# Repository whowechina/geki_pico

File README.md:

# Geki Pico - ONGEKI Style Mini Controller
[点这里可以切换到中文版](README_CN.md)

Features:
* It's small but closely replicates the feel of the arcade controller.
* Smooth lever action with adjustable resistance.
* Air WAD with sound feedback.
* IO4 emulation.
* Built-in AIME card reader.
* Command line for configurations.
* All source files open.

Thanks to many respectful guys/companies who made their tools or materials free or open source (KiCad, OnShape, InkScape, Raspberry things).

Special thanks to community projects and developers.

* Robin Grosset (https://github.com/rgrosset/pico-pwm-audio)
* GEEKiDoS (https://github.com/GEEKiDoS/ongeeki-firmware)
* Pololu (https://github.com/pololu/vl53l0x-arduino, https://github.com/pololu/vl53l1x-arduino)
* RP_Silicon_KiCad: https://github.com/HeadBoffin/RP_Silicon_KiCad
* Type-C: https://github.com/ai03-2725/Type-C.pretty
* Chris Veigl (https://github.com/ChrisVeigl/ESP32Sound)

## My Other Projects
You can check out my other cool projects.

* Popn Pico: https://github.com/whowechina/popn_pico
* IIDX Pico: https://github.com/whowechina/iidx_pico
* IIDX Teeny: https://github.com/whowechina/iidx_teeny
* Chu Pico: https://github.com/whowechina/chu_pico
* Mai Pico: https://github.com/whowechina/mai_pico
* Diva Pico: https://github.com/whowechina/diva_pico
* AIC Pico: https://github.com/whowechina/aic_pico
* Groove Pico: https://github.com/whowechina/groove_pico
* Geki Pico: https://github.com/whowechina/geki_pico
* Musec Pico: https://github.com/whowechina/musec_pico
* Ju Pico: https://github.com/whowechina/ju_pico
* Bishi Pico: https://github.com/whowechina/bishi_pico
* Bishi Pico: https://github.com/whowechina/nos_pico

## **Disclaimer** ##
I made this project in my personal time with no financial benefit or sponsorship. I will continue to improve the project. I have done my best to ensure that everything is accurate and functional, there's always a chance that mistakes may occur. I cannot be held responsible for any loss of your time or money that may result from using this open source project. Thank you for your understanding.

## About the License
It's CC-NC. So DIY for yourself and for your friend, don't make money from it. And plagiarism that doesn’t even dare to mention the original author is not acceptable. Plase note that pooling orders and group buying for raw materials is acceptable. Selling off any leftover components without profit is also acceptable.

If you're interested in buying from me or some kind of commercial use, please contact me (Discord, QQ group, Wechat group or leave your contact in issue section).

## My Discord Invitation
https://discord.gg/M8f2PPQFEA

## HOW TO BUILD
### PCB and Components
* Go JLCPCB and make order with the gerber zip file (latest `Production\PCB\geki_main_xxx.zip`), regular FR-4 board, black or white color, **1.6mm** thickness.  
  
* 1x Rasberry Pico Pi Pico or pin-to-pin compatible clones (U1).  
  https://www.raspberrypi.com/products/raspberry-pi-pico
* 1x USB Type-C socket (918-418K2023S40001 or KH-TYPE-C-16P)
* 35x WS2812B-4020 side-facing RGB LEDs (D2-D36). Be careful with the orientation when soldering: D2 to D4 and D34 to D36 should be facing sideways, while the others should be facing up.  
  https://www.lcsc.com/product-detail/Light-Emitting-Diodes-LED_Worldsemi-WS2812B-4020_C965557.html
* 2x WS2812B-3528 RGB LEDs (D1, D37).
* 2x 8002A audio mini amplifier board (AMP1, AMP2), or you can use discrete components following the schematics (R4, R5, R8, R9, C9 ~ 12).  
    
  https://www.nz-electronics.co.nz/products/4pcs-one-sell-3v-5v-supply-voltage-3w-8002-audio-player-power-amplifier-module-board-pcb-mono  
  https://www.ebay.com.au/itm/225481264605

* 4x VL53L0x ToF sensors (two sensors on each side), get the optical covers too.  
  https://kuriosity.sg/products/time-of-flight-tof-distance-sensor-vl53l0x-200cm-with-optical-cover  
  https://www.smart-prototyping.com/VL53L0X-ToF-Distance-Sensor  
  You can also use 2x VL53L0x or VL53L1x, meaning each side only has one sensor. The performance is slightly worse.  
  https://www.amazon.com/Soaying-VL53L1X-Distance-Measurement-Extension/dp/B0CTHC43SV

* 4x SH1.0 4-pin right angle SMD connectors (TOF1, TOF2, TOF3, TOF4), and some SH1.0 4P cables to connect the ToF sensors. This is optional as you can always hand wire them.

* 2x Small speakers no larger than 20mm\*20mm\*5mm, 8ohm or close, (SPK1, SPK2), you can even harvest similar sized ones from old broken toys.  
  Try search on Google with keywords: "smd speaker 1540"

* 1x SS49E linear Hall sensor (U5).  
  https://mou.sr/4gDuQKu  
  https://www.digikey.com/short/fmm54dzq
* 1x LP5907MFX-4.5 or TPS7A2042PDBVR LDO, in SOT23-5 (U7).
* 2x SMD capacitors, 22uF, 10V or higher, 6.3\*5.8mm (diameter\*height) (C16, C17), MLCC ones work too.
* 10x 0603 0.1uF (0.1~1uF all fine) capacitors (C1 to C8, CC1 and CC2), OPTIONAL but strongly recommended.
* 3x 0603 5.1kohm resistors, (R1, R2, R7).
* 1x 0603 10ohm resistor, (1-20ohm all work fine) (R3, removed in new versions).
* 1x 0603 2kohm resistor (R6).

* 8x Kailh Choc v1 or v2 switches (2 of them must be Choc v1). Choose linear ones, such as "Red Pro" or the latest Lofree branded Ghost.  

* 1x PN532 Module (the Red Square board version, cheap clones work too). It's optional, if you want a built-in card reader, then you need it.    
  https://www.elechouse.com/product/pn532-nfc-rfid-module-v4/

* If you're using 8002A boards, leave R4, R5, R8, R9, C9 ~ 12, U3, U4 empty.
* Leave U2 empty, it only provides placebo effect for better ADC reference voltage.

* This is how it looks after soldering.  

* Becareful of 2 pin holes. It's a common oversight to either forget to solder them or to leave air bubbles during the process. To avoid this, solder slowly from one side of the hole, using minimal solder wire and a generous amount of flux.  

### 3D Printing
* Printing parameters  
  * PLA or PETG.
  * Layer height: 0.2mm
  * Support: Yes, always.

#### Lever Parts
* Lever Base: `Production\3DPrint\geki_pico_lever_base.stl`, white.
* Lever Rotator: `Production\3DPrint\geki_pico_lever_rotator_*mm.stl`, white, choose the one that matches your magnet diameter.
* 2x Lever Fixer: `Production\3DPrint\geki_pico_lever_fixer.stl`, or 1x Intergral Lever Fixer (`Production\3DPrint\geki_pico_lever_fixer_integral.stl`), white. 
* Lever Handle: `Production\3DPrint\geki_pico_lever_handle.stl`, red.

#### Housing Parts
You need to rotate 135 degrees on Z axis to fit the bed.

* Housing Bottom: `Production\3DPrint\geki_pico_bottom.stl`, I chose sakura pink, what's your choice?
* Housing Support: `Production\3DPrint\geki_pico_support_*.stl`, semi-transparent. Choose the one that matches your ToF sensor configuration.
* Housing Top: `Production\3DPrint\geki_pico_top.*`, white. If you have multi-color printing equipment and skill, use the 3mf one (button outlines and logo are black).

#### Button Caps
* 6x Main Button Cap: `Production\3DPrint\geki_pico_button_main_choc_*.stl`, white, print up-side down so you get nice button surface and stem. Choc v1 and v2 are different, choose the right one.
* 2x Aux Button Cap: `Production\3DPrint\geki_pico_button_aux.stl`, semi-transparent, print up-side down.

### Lever
* Required components
  * PTFE or UHMW Film Tape, >=10mm wide, >=0.3mm (0.5mm is best) thick, one-side adhesive.  
    https://www.3m.com/3M/en_US/p/d/b40072069/
  * 2x MR117ZZ bearings (7mm inner diameter, 11mm outer diameter, 3mm thickness), go with cheap ones, they work just as great.  
    https://www.amazon.com/s?k=mr117zz
  * 1x Double-ended stud screws, M4 thread, 50mm or 55mm total length. Please note that the threaded length should not exceed 16mm.  
    https://www.amazon.com/METALLIXITY-Double-Screws-Stainless-Threaded/dp/B0B7BM6Y4M
  * 1x round magnet with **5mm** or **6mm** diameter, **2mm** to **3.5mm** tall, MUST be radially/diametrically magnetized (N-S poles on the curved side).  
    https://wargameportal.com/products/special-diametrically-magnetized-50pcs-5mm-x-2mm-3-16-x-1-16-disc-magnets?variant=49014932209942
  * 6x **M2*6mm regular screws** for resistance adjustment.
  * 4x **M2*16mm regular screws** for fixing the bearings.
  * Optional: Some damping grease.
* Assemble Steps
  1. Print out the parts.  
      
  2. Stick PTFE/UHMW tape to the sliding surfaces of the fixer and the rotator. Then trim the tape to match the surface shape. If you have some damping grease (medium or medium-high stickiness), apply a tiny bit on the sliding surfaces. Turn the M2*6mm screws into the bearing fixers halfway, don’t and never tighten them.  
      
  3. Install the 2 bearings on both sides of the rotator and put it in the base, then use M2*16mm screws to fix the two bearing fixers on the base.  
     
  4. Use some instant glue to stick the magnet to the bottom of the rotator. Make sure the poles are placed horizontally. A little trick is you connect several magnets together and draw a line to cross all the magnets, and then you know the poles.  
     
  5. Install the lever handle onto the double-ended stud screw, put aside. Later when the housing is ready we need to screw it into the lever rotator.  

### Assembly
* Other components needed
  * 4x **M3\*8mm regular screws** for fixing the lever to the bottom.
  * 8x **M3\*16mm regular screws** for the housing.
  * Some VHB double-sided tape to fix the speakers and the ToF sensors.
  * Some thin soft wires for the speakers and the ToF sensors.

* Steps
  1. Install the lever to the bottom part, using M3\*8mm screws.
  2. Wire (solder) the ToF sensors to the main PCB, each needs 4 wires.  
     If you're using an older PCB that only supports one sensor on each side, you can manually wire the secondary sensor. The secondary sensor uses the same SDA, SCL and GND pins as the primary sensor, but the VCC pin should be directly connected to the pins of the Pico, GP7 is for the right secondary sensor, GP9 is for the left secondary sensor.
  3. Use VHB tape to fix the ToF sensors on the ToF seats on the bottom part.
  4. Wire (solder) the speakers to the main PCB, each needs 2 wires.
  5. Use VHB tape to fix the speakers on the floor of the bottom part.
  6. Install the main PCB to the bottom part, no screws needed.
  7. Bend the hall-effect sensor (SS49E) so it stays on top of the lever magnets. Remember to leave a tiny gap so the rotator can move freely.  
     
  8. Solder the PN532 module, 8002A modules to the main PCB if you haven't done it yet.
  9. Install the main button caps and the aux button caps onto the switches.
  10. Now it looks like this. Please note that in the picture it is the PCB v1. I've done some optimizations in the later version.  
    
  11. Now it's the perfect chance to adjust the lever resistance. Slowly and gently turn the M2 screws to adjust the tension on the sliding surface. You may need to turn all the screws evenly.
  12. Put the support part on the bottom part, then put the top part on the support part.
  13. Align these parts and use M3\*20mm screws to fix them together. You may need to carefully adjust the position of the ToF sensors so the IR cover (or the tiny sensor chip) fit into the windows on the support part.
  14. Finally screw the lever handle into the lever rotator.  

### Firmware
* UF2 file is in `Production\Firmware` folder.
* For the new build, hold the BOOTSEL button while connect the USB to a PC, there will be a disk named "RPI-RP2" showed up. Drag the UF2 firmware binary file into it. That's it. There's a small hole at the bottom side of the Geki Pico, it is facing right to the BOOTSEL button.
* If it's already running Geki Pico firmware, you can either use "update" in command line or hold down at least 4 buttons while connecting to USB to enter update mode.
* To access the command line, you can use this Web Serial Terminal to connect to the USB serial port of the Geki Pico. (Note: "?" is for help)  
  https://googlechromelabs.github.io/serial-terminal/

### Usage
* You need to calibrate the lever by "lever calibrate" command after you flash the firmware.
* If you feel the lever direction is in correct, you can use "lever invert \<on|off\>" command to change it.
* Volume of sound feedback can be set by "volume \<0~255\>" command.
* ToF sensors have triggering zones, the purple zones are for the WAD, the orange zone is for SHIFT.  
   
* To emulate IO4 TEST/SERVICE/COIN, you can put your hand in SHIFT zone. When you see the WAD lights flashing, the AUX buttons become TEST and SERVICE, and swinging the lever for "INSERT COINS".
* AIME is on a secondary COM port. You can set mode or toggle virtual AIC function.
* ToF mixing algorithms in dual sensor each side configuration.
  * `primary` and `secondary`: always use primary or secondary sensor, fallback to the other one if the chosen one has no reading, `strict` option means no fallback.
  * `max` and `min`: use the larger or smaller reading of the two sensors, `strict` option means if one sensor has no reading, result will be no reading.
  * `average`: use the average of the two sensors, `window` option means readings from both sensors must be within a certain range, otherwise result will be no reading. `window` set to 0 means no range check.
* You can set trigger window for left WAD, right WAD and shift by `tof trigger <left|right|shift> ...` command. The window is in millimeters. In is the window to trigger, out is the window to release.
* You can use `tof diagnose [on|off]` command to toggle diagnose mode. In diagnose mode, the ToF sensor will continuously print the raw distance data from all sensors. It's useful for diagnostics.

## CAD Source File
I'm using OnShape free subscription. It's powerful but it can't archive original designs to local, so I can only share the link here. STL/DXF/DWG files are exported from this online document.  
  https://cad.onshape.com/documents/eb38f3add988969c42b50060/w/86bcbeae8562f01c1a81c53e/e/feecb6f371a076c968584d3c

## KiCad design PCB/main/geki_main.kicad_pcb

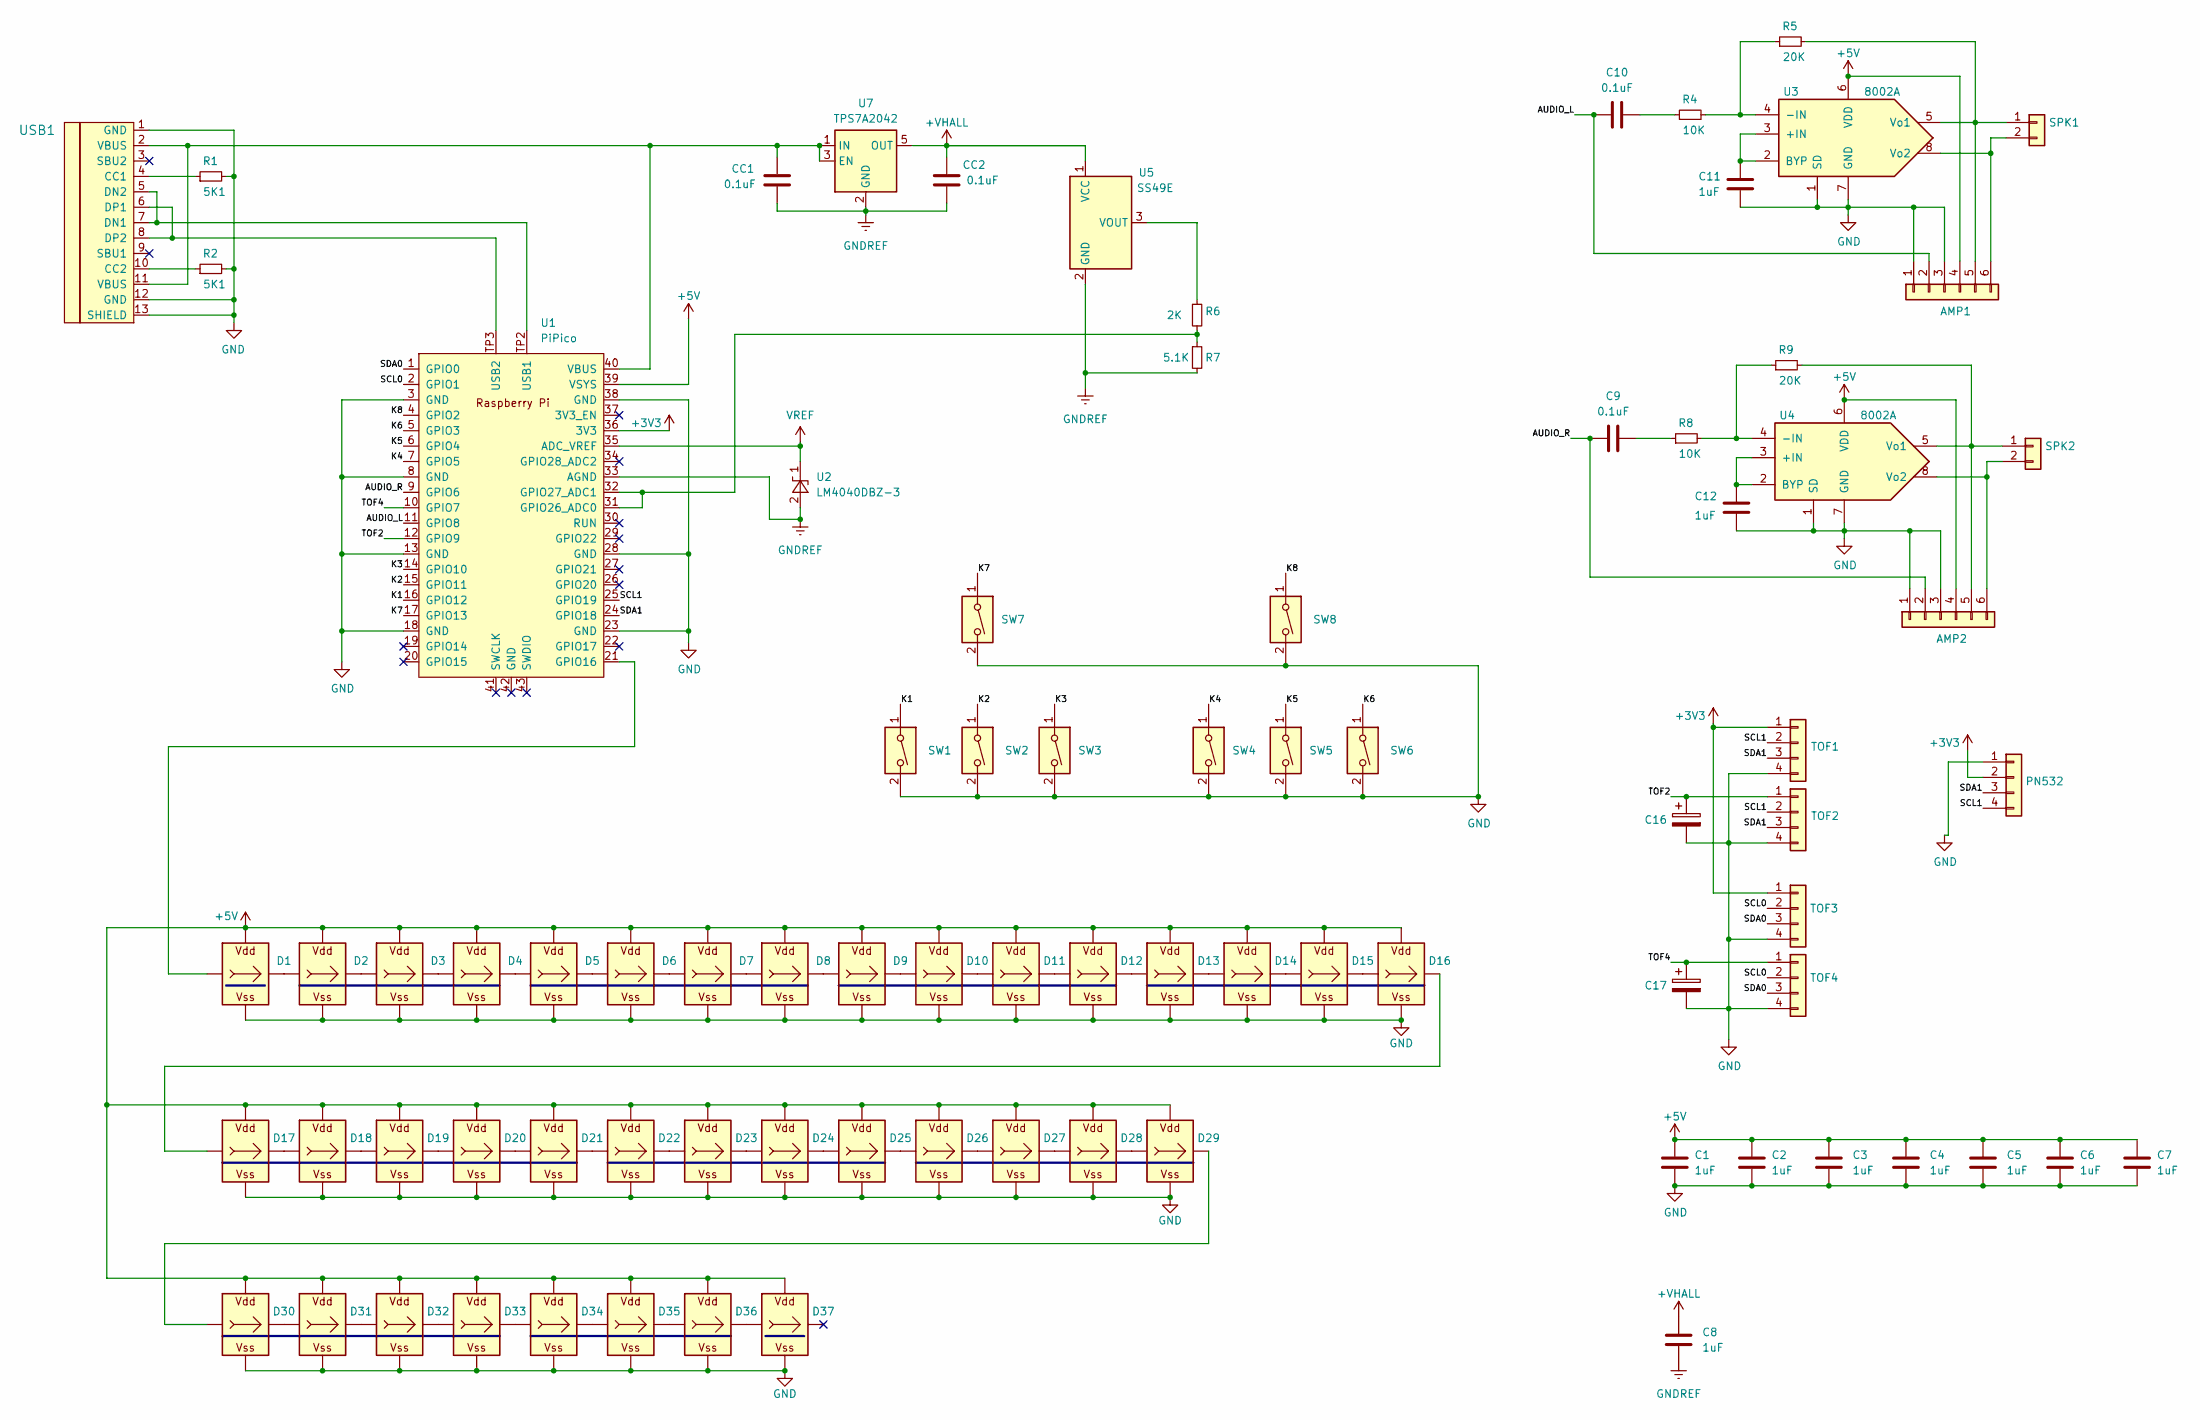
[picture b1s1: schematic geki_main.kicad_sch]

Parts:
AMP1, AMP2: Conn_01x06; 8002A_TAP
C1, C2, C3, C4, C5, C6, C7, C8, C11, C12: 1uF; C_0603_1608Metric_Pad1.08x0.95mm_HandSolder
C9, C10: 0.1uF; C_0603_1608Metric_Pad1.08x0.95mm_HandSolder
C16, C17: 10uF; CP_Elec_6.3x3
CC1, CC2: 0.1uF; C_0603_1608Metric_Pad1.08x0.95mm_HandSolder
D1, D37: WS2812B_Unified; WS2812B-2835
D2, D3, D4, D34, D35, D36: WS2812B_Unified; WS2812B-4020
D5, D6, D7, D8, D9, D10, D11, D12, D13, D14, D15, D16, D17, D18, D19, D20, D21, D22, D23, D24, D25, D26, D27, D28, D29, D30, D31, D32, D33: WS2812B_Unified; WS2812B-4020_UP
PN532: Conn_01x04; PinHeader_1x04_P2.54mm_Vertical
R1, R2: 5K1; R_0603_1608Metric_Pad0.98x0.95mm_HandSolder; LCSC C23186
R4, R8: 10K; R_0603_1608Metric_Pad0.98x0.95mm_HandSolder; LCSC C23186
R5, R9: 20K; R_0603_1608Metric_Pad0.98x0.95mm_HandSolder; LCSC C23186
R6: 2K; R_0603_1608Metric_Pad0.98x0.95mm_HandSolder; LCSC C23186
R7: 5.1K; R_0603_1608Metric_Pad0.98x0.95mm_HandSolder; LCSC C23186
SPK1, SPK2: Conn_01x02; Solder_2P
SW1, SW2, SW3, SW4, SW5, SW6, SW7, SW8: SW_DIP_x01; SW_Kailh_Choc_V1V2_1.00u_LED
TOF1, TOF2, TOF3, TOF4: Conn_01x04; SH1.0_4P_Solder_Combo
U1: PiPico; RPi_Pico_SMD_Pins
U2: LM4040DBZ-3; SOT-23
U3, U4: 8002A; SO-8_3.9x4.9mm_P1.27mm
U5: SS49E; SS49E_Bend
U7: TPS7A2042; SOT-23-5
USB1: U262-161N-4BVC11; HRO-TYPE-C-31-M-12-Assembly; LCSC C319148

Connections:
+3V3: PN532.2, TOF1.1, TOF3.1, U1.36 (3V3)
+5V: AMP1.4, AMP2.4, C1.1, C2.1, C3.1, C4.1, C5.1, C6.1, C7.1, D1.V (VDD), D2.V (VDD), D3.V (VDD), D4.V (VDD), D5.V (VDD), D6.V (VDD), D7.V (VDD), D8.V (VDD), D9.V (VDD), D10.V (VDD), D11.V (VDD), D12.V (VDD), D13.V (VDD), D14.V (VDD), D15.V (VDD), D16.V (VDD), D17.V (VDD), D18.V (VDD), D19.V (VDD), D20.V (VDD), D21.V (VDD), D22.V (VDD), D23.V (VDD), D24.V (VDD), D25.V (VDD), D26.V (VDD), D27.V (VDD), D28.V (VDD), D29.V (VDD), D30.V (VDD), D31.V (VDD), D32.V (VDD), D33.V (VDD), D34.V (VDD), D35.V (VDD), D36.V (VDD), D37.V (VDD), U1.39 (VSYS), U3.6 (VDD), U4.6 (VDD)
+VHALL: C8.1, CC2.1, U5.1 (VCC), U7.5 (OUT)
/AUDIO_L: AMP1.2, C10.1, U1.11 (GPIO8)
/AUDIO_R: AMP2.2, C9.1, U1.9 (GPIO6)
/K1: SW1.1, U1.16 (GPIO12)
/K2: SW2.1, U1.15 (GPIO11)
/K3: SW3.1, U1.14 (GPIO10)
/K4: SW4.1, U1.7 (GPIO5)
/K5: SW5.1, U1.6 (GPIO4)
/K6: SW6.1, U1.5 (GPIO3)
/K7: SW7.1, U1.17 (GPIO13)
/K8: SW8.1, U1.4 (GPIO2)
/SCL0: TOF3.2, TOF4.2, U1.2 (GPIO1)
/SCL1: PN532.4, TOF1.2, TOF2.2, U1.25 (GPIO19)
/SDA0: TOF3.3, TOF4.3, U1.1 (GPIO0)
/SDA1: PN532.3, TOF1.3, TOF2.3, U1.24 (GPIO18)
/TOF2: C16.1, TOF2.1, U1.12 (GPIO9)
/TOF4: C17.1, TOF4.1, U1.10 (GPIO7)
GND: AMP1.1, AMP1.3, AMP2.1, AMP2.3, C1.2, C2.2, C3.2, C4.2, C5.2, C6.2, C7.2, C11.1, C12.1, C16.2, C17.2, D1.G (VSS), D2.G (VSS), D3.G (VSS), D4.G (VSS), D5.G (VSS), D6.G (VSS), D7.G (VSS), D8.G (VSS), D9.G (VSS), D10.G (VSS), D11.G (VSS), D12.G (VSS), D13.G (VSS), D14.G (VSS), D15.G (VSS), D16.G (VSS), D17.G (VSS), D18.G (VSS), D19.G (VSS), D20.G (VSS), D21.G (VSS), D22.G (VSS), D23.G (VSS), D24.G (VSS), D25.G (VSS), D26.G (VSS), D27.G (VSS), D28.G (VSS), D29.G (VSS), D30.G (VSS), D31.G (VSS), D32.G (VSS), D33.G (VSS), D34.G (VSS), D35.G (VSS), D36.G (VSS), D37.G (VSS), PN532.1, R1.2, R2.2, SW1.2, SW2.2, SW3.2, SW4.2, SW5.2, SW6.2, SW7.2, SW8.2, TOF1.4, TOF2.4, TOF3.4, TOF4.4, U1.3 (GND), U1.8 (GND), U1.13 (GND), U1.18 (GND), U1.23 (GND), U1.28 (GND), U1.38 (GND), U3.1 (SD), U3.7 (GND), U4.1 (SD), U4.7 (GND), USB1.1 (GND), USB1.12 (GND), USB1.13 (SHIELD)
GNDREF: C8.2, CC1.2, CC2.2, R7.2, U1.33 (AGND), U2.2 (A), U5.2 (GND), U7.2 (GND)
unnamed: AMP1.5, R5.2, SPK1.1, U3.5 (Vo1)
unnamed: AMP1.6, SPK1.2, U3.8 (Vo2)
unnamed: AMP2.5, R9.2, SPK2.1, U4.5 (Vo1)
unnamed: AMP2.6, SPK2.2, U4.8 (Vo2)
unnamed: C9.2, R8.1
unnamed: C10.2, R4.1
unnamed: D1.I (In), U1.21 (GPIO16)
unnamed: D1.O (Out), D2.I (In)
unnamed: D2.O (Out), D3.I (In)
unnamed: D3.O (Out), D4.I (In)
unnamed: D4.O (Out), D5.I (In)
unnamed: D5.O (Out), D6.I (In)
unnamed: D6.O (Out), D7.I (In)
unnamed: D7.O (Out), D8.I (In)
unnamed: D8.O (Out), D9.I (In)
unnamed: D9.O (Out), D10.I (In)
unnamed: D10.O (Out), D11.I (In)
unnamed: D11.O (Out), D12.I (In)
unnamed: D12.O (Out), D13.I (In)
unnamed: D13.O (Out), D14.I (In)
unnamed: D14.O (Out), D15.I (In)
unnamed: D15.O (Out), D16.I (In)
unnamed: D16.O (Out), D17.I (In)
unnamed: D17.O (Out), D18.I (In)
unnamed: D18.O (Out), D19.I (In)
unnamed: D19.O (Out), D20.I (In)
unnamed: D20.O (Out), D21.I (In)
unnamed: D21.O (Out), D22.I (In)
unnamed: D22.O (Out), D23.I (In)
unnamed: D23.O (Out), D24.I (In)
unnamed: D24.O (Out), D25.I (In)
unnamed: D25.O (Out), D26.I (In)
unnamed: D26.O (Out), D27.I (In)
unnamed: D27.O (Out), D28.I (In)
unnamed: D28.O (Out), D29.I (In)
unnamed: D29.O (Out), D30.I (In)
unnamed: D30.O (Out), D31.I (In)
unnamed: D31.O (Out), D32.I (In)
unnamed: D32.O (Out), D33.I (In)
unnamed: D33.O (Out), D34.I (In)
unnamed: D34.O (Out), D35.I (In)
unnamed: D35.O (Out), D36.I (In)
unnamed: D36.O (Out), D37.I (In)
unnamed: R6.2, R7.1, U1.31 (GPIO26_ADC0), U1.32 (GPIO27_ADC1)
unnamed: U1.TP2 (USB1), USB1.5 (DN2), USB1.7 (DN1)
unnamed: U1.TP3 (USB2), USB1.6 (DP1), USB1.8 (DP2)
unnamed: CC1.1, U1.40 (VBUS), U7.1 (IN), U7.3 (EN), USB1.2 (VBUS), USB1.11 (VBUS)
unnamed: C11.2, U3.2 (BYP), U3.3 (+IN)
unnamed: R4.2, R5.1, U3.4 (-IN)
unnamed: C12.2, U4.2 (BYP), U4.3 (+IN)
unnamed: R8.2, R9.1, U4.4 (-IN)
unnamed: R6.1, U5.3 (VOUT)
unnamed: R1.1, USB1.4 (CC1)
unnamed: R2.1, USB1.10 (CC2)
VREF: U1.35 (ADC_VREF), U2.1 (K)

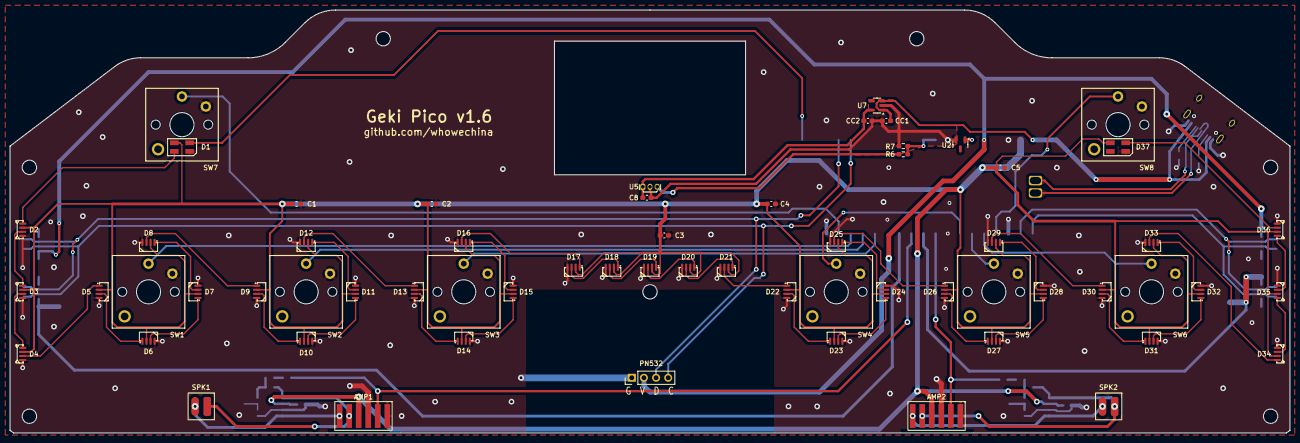
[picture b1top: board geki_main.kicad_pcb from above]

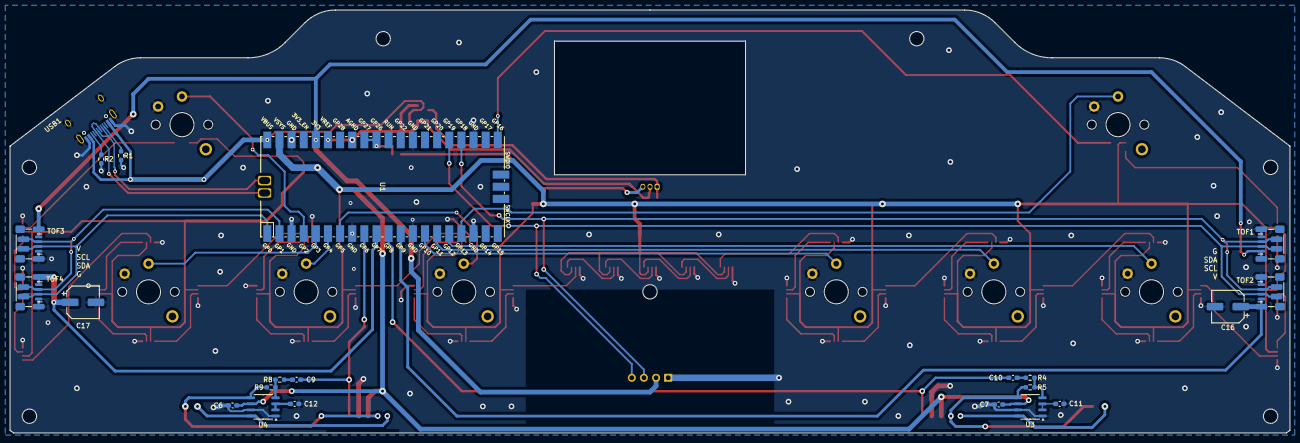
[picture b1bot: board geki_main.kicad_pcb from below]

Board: 2 copper layers, 268.0 x 88.6 mm, 85 parts (22 on the bottom side), 76 nets.

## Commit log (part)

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2023-09-29 Start PCB work
2023-09-29 gitignore update
2023-10-22 Some update (8002A added)
2024-09-03 PCB - a dirty start
2024-09-04 Some update, progress 60%
2024-09-04 PCB progress 80%
2024-09-05 PCB v1.0
2024-09-10 Firmware initial version
2024-09-13 IO4 HID
2024-09-13 Sounds for WAD
2024-09-13 Enable Sound
2024-09-15 PCB v1.1 (DCDC and PN532)
2024-09-15 Better airkey process
2024-09-15 AIC submodule included
2024-09-16 PCB v1.2 for direct PN532 soldering
2024-09-16 Kinda works with game
2024-09-16 Sound volume and complete io4
2024-09-17 Finished for publish
2024-09-17 Sliding surface lubricant
2024-09-17 Small notice for RGB 4020 facing
2024-09-17 Lever resistance adjustment
2024-09-17 Small typo fix in doc
2024-09-17 Update lever commands
2024-09-18 ToF zones in doc
2024-09-18 IR cover warning
2024-09-18 ToF with no optical cover
2024-09-19 README_CN ready
2024-09-19 Typo fix
2024-09-21 Refactor of vl53l0x
2024-09-22 Vl53L1x code (not enabled yet)
2024-09-22 Identifies VL53L1x
2024-09-22 Less wobble keycap
2024-09-22 VL53L1x working
2024-09-22 Smaller ROI for better stability
2024-09-24 Update 3DPrint folder
2024-09-26 Fix cache crosstalk
2024-09-26 ROI setting in CLI
2024-09-30 VL53L1x in README
2024-10-02 Fix bearing models in README
2024-10-02 Update license part in README
2024-10-02 Small wording update
2024-10-04 6mm magnet option added
2024-10-05 Add discrete step-up converter option
2024-10-11 Add firmware build for pico 2
2024-10-11 Fix parameters for housing screws
2024-10-12 Fix cli invalid character and lever calibration range
2024-10-12 cli.c follow upload for last commit
2024-10-12 Revert "cli.c follow upload for last commit"
    This reverts commit b06ca7e58df6f2a6292cd14f04e9c3baf1b5e21a.
2024-10-13 Auto slave address for instances
2024-10-14 Improve lever combo
2024-10-18 Cross-reference and Discord invitation
2024-10-28 Fix a typo in CN guide
2024-11-02 Block input of illegal characters
    Block input of illegal characters
2024-11-02 Fix typo in usb_descriptors.c
    Change "Mai Pico AIME Port"
    to "Geki Pico AIME Port"
2024-11-04 Fix a typo in USB descriptor
2024-11-04 Mix for multiple ToF
2024-11-04 Joy to IO4 and cleanup
2024-11-04 Separate tof mix and key triggering
2024-11-05 Tof runtime diagnose feature
2024-11-05 Trigger window setting
2024-11-05 PCB v1.4 supports dual ToF
2024-11-05 4x ToF for better WAD performance
2024-11-06 Dual sensor mode optimization and doc
2024-11-18 Better lever slots and button holes
2024-11-23 Cross-reference
2024-11-23 Rename shaft to rotator
2024-11-29 Fix getchar return handling
2024-12-02 Fix ToF i2c write timing
2024-12-02 Fix a small typo
2024-12-07 PCB v1.5 (remove the slider option)
2024-12-30 Shorter thread version bolt for the lever
2024-12-30 Notes on bolt threaded length
2025-01-04 Change WAD sounds
2025-01-04 Better polling rate
2025-01-10 PCB v1.51, footprint finetune
2025-01-12 Add ribs to bottom part
2025-01-12 PCB v1.52 to stabilize performance of aux ToFs
2025-02-05 GPIO based WAD as ToF fallback
2025-03-12 Enlarge tof avg judge window
2025-03-25 Updage guide for latest PCB version
2025-04-04 Hot boot can detect secondary tof
2025-04-04 Cross-reference to Nos Pico
2025-04-05 Small fix that may help power ripple
2025-07-02 Button statistics
2025-09-06 ToF GPIO power off before detect
2025-11-30 Prepare for external LED strip
2025-11-30 External LED strip and support LED data from segatools
2025-12-01 WAD lights respond to fallback buttons
2025-12-05 Shorter HID timeout
2025-12-05 Shift indication on aux leds
